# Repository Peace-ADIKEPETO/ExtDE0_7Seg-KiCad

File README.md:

# ExtDE0_7Seg – KiCad port (through-hole, hand-made sandwich PCB)

Extension board for the Terasic **DE0** FPGA board: 4-digit 7-segment display, 8 DIP switches with LEDs, 4 push buttons with LEDs, and a 5-way joystick, all connected through the DE0 40-pin GPIO header.

This repository is a **KiCad re-capture and rework** of the original EPFL/LAP design, adapted to parts that are easy to source in Benin and to a home-made fabrication process.

> **Credit.** The original design is *ExtDE0_7Seg*, EPFL/LAP, R. Beuchat, Rev A, 01/2013 (Altium). The schematic structure and the I/O concept come from that work. Check the original author's licence/terms before publishing this repository, and keep this credit.

## Status

| Item | State |
|---|---|
| Schematic (KiCad, hierarchical, 5 sheets + root) | Done, ERC clean |
| Footprints assigned | Done |
| PCB routing (Freerouting) | Done, GND handled by a pour on B.Cu |
| DRC | 0 errors, 0 unconnected pads, silkscreen warnings only (checked 2026-08-27) |
| Gerber / drill export | Not done yet |
| Board fabricated | No |
| Hardware tested | **No** |

Nothing here has been built or powered yet. See [Known risks](#known-risks-to-check-before-powering-up).

## What changed compared to the original

| Area | Original (2013) | This version | Why |
|---|---|---|---|
| Parts | SMD (0603, SOT-23, resistor arrays) | All through-hole, discrete resistors | Hand soldering, home etching, local sourcing |
| Display | 6-digit KEM-3061-ASR (+ 4-digit LTC4627JR fallback), common anode | One 4-digit 5641AS-style module, **common cathode** | The 6-digit part is not obtainable |
| Digit select | pMOS, active low | nMOS (2N7000), active high | Common cathode must be sunk to GND |
| Segment select | nMOS, active high | pMOS (IRF9520), active low | Common cathode needs segments sourced from 3V3 |
| Reset (discharge) transistors | nMOS | pMOS to 3V3 | Opposite polarity, same purpose |
| P1 header | Generic 2x20 | 2x20 **female** socket (PinSocket 2.54 mm) | Plugs onto the DE0 GPIO pins |
| Fabrication | Industrial 2-layer | Two single-sided boards glued back to back | Material constraint, see below |

### Net names in the KiCad project

The KiCad nets still use some of the original names (`nSelDig0..3`, `SelSeg0..7`, `Reset_Led`) even though the polarity of those lines changed with the common-cathode rework. The names are misleading. Read the table below, not the names.

| Net | Drives | Active level (as built) |
|---|---|---|
| `nSelDig0..3` | Gate of 2N7000 (digit select, source to GND) | **High** |
| `SelSeg0..7` | Gate of IRF9520 (segment, source to 3V3) | **Low** |
| `Reset_Led` | Gates of the 4 reset pMOS (source to 3V3) | **Low** |

Your FPGA code (HDL) must follow these levels. Consider renaming the nets in a later revision.

## Hardware

### Bill of materials (summary)

| Ref | Part | Qty | Package |
|---|---|---|---|
| U1 | 4-digit 7-segment, common cathode (5641AS-style, 0.56") | 1 | THT, custom footprint |
| Digit select | 2N7000 (nMOS) | 4 | TO-92 |
| Segment select | IRF9520 (pMOS) | 8 | TO-220 |
| Reset | IRF9520 (pMOS) | 4 | TO-220 |
| Joystick | Alps SKQUDBE010, 5-way | 1 | Footprint converted from the SMD model, see notes |
| Push buttons | 6x6 mm, 4-pin tactile | 4 | THT |
| DIP switch | 8 positions | 1 | THT |
| LEDs | Yellow, green, orange, red x9 (D1 to D12) | 12 | 3 mm or 5 mm |
| Resistors | 4.7k, 1k, 560R, 330R, 100R, 56R, 0R (axial 1/4 W) | see KiCad BOM | THT |
| P1 | 2x20 female header, 2.54 mm | 1 | THT |

The authoritative list is the BOM exported from KiCad, not this table.

### Sheets

1. **Joystick** – five switches to GND, 4.7k pull-ups to 3V3, outputs `nJoystickN/S/E/W/C` (active low).
2. **Sw_LEDs** – 8-position DIP switch, two resistors and one LED per channel, outputs `Sw_Led0..7`.
3. **LED_Buttons** – 4 buttons with 4.7k pull-ups (`nButton0..3`, active low) and 4 independent LEDs driven by `LedButton0..3`.
4. **6Dig7Seg (4-digit)** – multiplexed display driver: digit-select nMOS, reset pMOS, segment-select pMOS, segment resistors.
5. **Connectors** – P1 (2x20 female) breakout of all nets.

Display multiplexing rule carried over from the original: select one digit at a time, and **never assert the reset transistor together with the digit select** of the same digit. A reset pulse is needed between two digit accesses.

## Fabrication: two-board sandwich

The design is drawn as a normal 2-layer board in KiCad. It is then built as two single-sided boards:

- **F.Cu = Board B**: signal traces, all components.
- **B.Cu = Board A**: GND pour (GND is not routed as traces).
- Every via is a hand-made wire link between the two boards.

Process:

1. Plot F.Cu + Edge.Cuts and B.Cu + Edge.Cuts as two separate artworks.
2. Etch both boards.
3. Clamp the two boards aligned and drill them together from the single drill file.
4. Solder a wire link in each via hole, then insert a thin insulating layer (leaving holes clear) and glue the boards.
5. Solder components from the board B side. Component leads only need to reach board A where the net is GND, or at a via.
6. Check continuity and shorts with a multimeter before applying power.

Design rules used: via 2.0 mm pad / 1.2 mm drill. Component hole minimum was lowered to match real leads. The GND zone uses thermal reliefs on THT pads to make hand soldering easier.

## Repository layout

```
7Seg_Ext.kicad_pro        KiCad project
7Seg_Ext.kicad_sch        root schematic
*.kicad_sch               sub-sheets
7Seg_Ext.kicad_pcb        board layout
docs/                     original PDF schematic (reference)
Gerber files/                   F.Cu and B.Cu plots, drill file (to be generated)
```

## Known risks to check before powering up

- **IRF9520 is not a logic-level MOSFET.** Driven from a 3.3 V FPGA pin its Vgs is only about -3.3 V, close to its threshold range. Segments may be dim or unreliable. Check the datasheet curves, and test one channel on a breadboard first. A logic-level pMOS (or a level-shifting stage) may be needed.
- **The common-cathode rework was derived by reasoning, not copied from the original netlist, and has not been simulated or tested.** Verify the display pinout and the segment/digit mapping against the real module with a multimeter.
- **P1 pin mapping** must match the DE0 GPIO header exactly. Verify every pin against the original PDF Connectors sheet and the DE0 manual before ordering copper.
- **Joystick footprint** was converted from an SMD model. Check pad positions and drill sizes against the Alps datasheet.
- **P1 orientation**: confirm pin 1 position, and that board thickness (two boards + insulator) still lets the socket seat on the DE0.
- **Alignment of the two boards** is the main mechanical risk. Drill them together.

## PCB layout

## PCB 3D Rendering

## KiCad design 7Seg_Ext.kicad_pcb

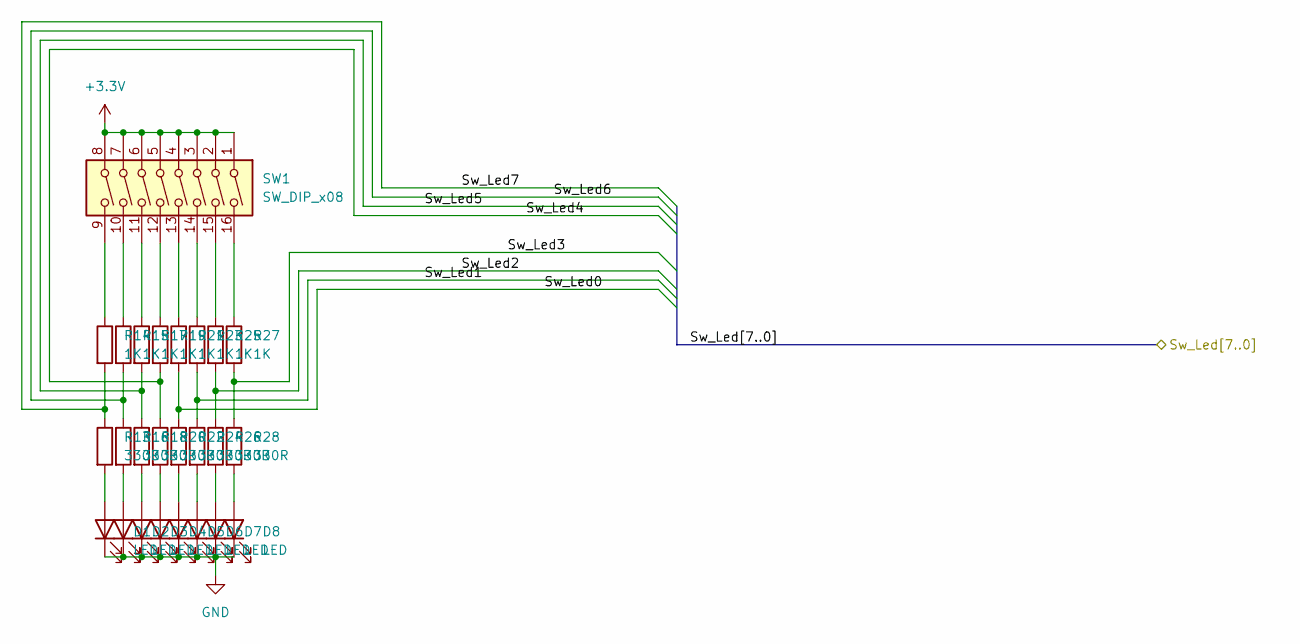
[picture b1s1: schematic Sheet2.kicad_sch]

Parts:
D1, D2, D3, D4, D5, D6, D7, D8: LED; LED_D3.0mm
R13, R16, R18, R20, R22, R24, R26, R28: 330R; R_Axial_DIN0207_L6.3mm_D2.5mm_P10.16mm_Horizontal
R14, R15, R17, R19, R21, R23, R25, R27: 1K; R_Axial_DIN0207_L6.3mm_D2.5mm_P7.62mm_Horizontal
SW1: SW_DIP_x08; SW_DIP_SPSTx08_Slide_9.78x22.5mm_W7.62mm_P2.54mm

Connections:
+3.3V: SW1.1, SW1.2, SW1.3, SW1.4, SW1.5, SW1.6, SW1.7, SW1.8; also elsewhere on the board
/Sw_Led0: R21.2, R22.1; also elsewhere on the board
/Sw_Led1: R23.2, R24.1; also elsewhere on the board
/Sw_Led2: R25.2, R26.1; also elsewhere on the board
/Sw_Led3: R27.2, R28.1; also elsewhere on the board
/Sw_Led4: R19.2, R20.1; also elsewhere on the board
/Sw_Led5: R17.2, R18.1; also elsewhere on the board
/Sw_Led6: R15.2, R16.1
/Sw_Led7: R13.1, R14.2; also elsewhere on the board
GND: D1.1 (K), D2.1 (K), D3.1 (K), D4.1 (K), D5.1 (K), D6.1 (K), D7.1 (K), D8.1 (K); also elsewhere on the board
unnamed: D1.2 (A), R13.2
unnamed: D2.2 (A), R16.2
unnamed: D3.2 (A), R18.2
unnamed: D4.2 (A), R20.2
unnamed: D5.2 (A), R22.2
unnamed: D6.2 (A), R24.2
unnamed: D7.2 (A), R26.2
unnamed: D8.2 (A), R28.2
unnamed: R14.1, SW1.9
unnamed: R15.1, SW1.10
unnamed: R17.1, SW1.11
unnamed: R19.1, SW1.12
unnamed: R21.1, SW1.13
unnamed: R23.1, SW1.14
unnamed: R25.1, SW1.15
unnamed: R27.1, SW1.16

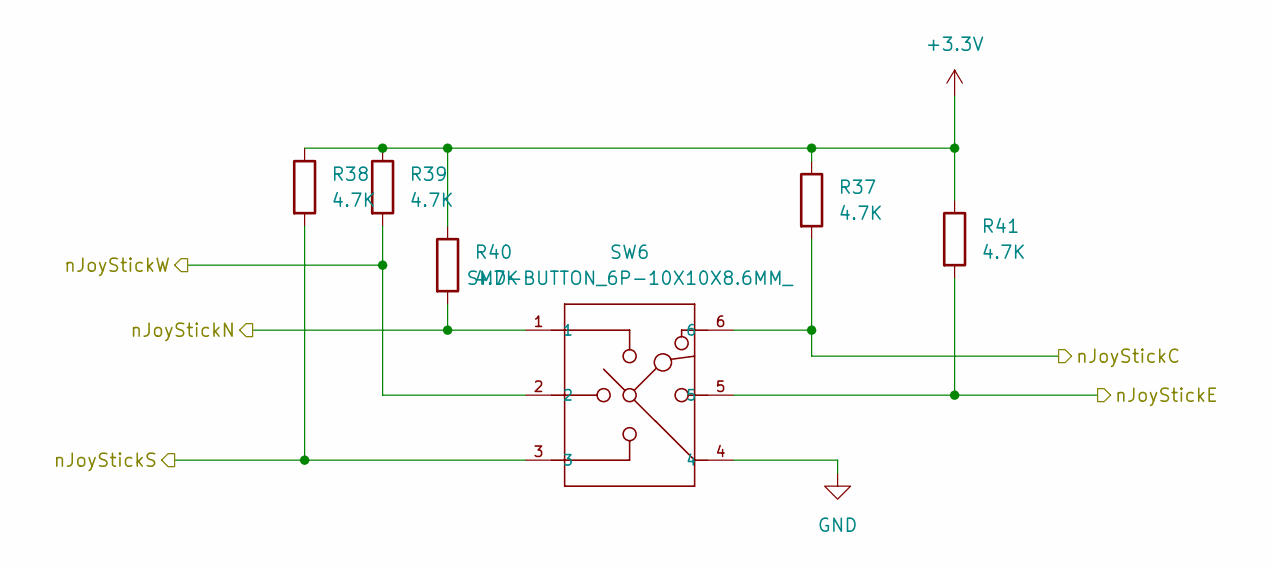
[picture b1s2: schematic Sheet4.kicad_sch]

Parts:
R37, R38, R39, R40, R41: 4.7K; R_Axial_DIN0207_L6.3mm_D2.5mm_P7.62mm_Horizontal
SW6: SMD-BUTTON_6P-10X10X8.6MM_; SW6-3.25-10X10X8.6MM

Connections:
+3.3V: R37.1, R38.1, R39.1, R40.1, R41.1; also elsewhere on the board
/nJoyStickC: R37.2, SW6.6; also elsewhere on the board
/nJoyStickE: R41.2, SW6.5; also elsewhere on the board
/nJoyStickN: R40.2, SW6.1; also elsewhere on the board
/nJoyStickS: R38.2, SW6.3; also elsewhere on the board
/nJoyStickW: R39.2, SW6.2; also elsewhere on the board
GND: SW6.4; also elsewhere on the board

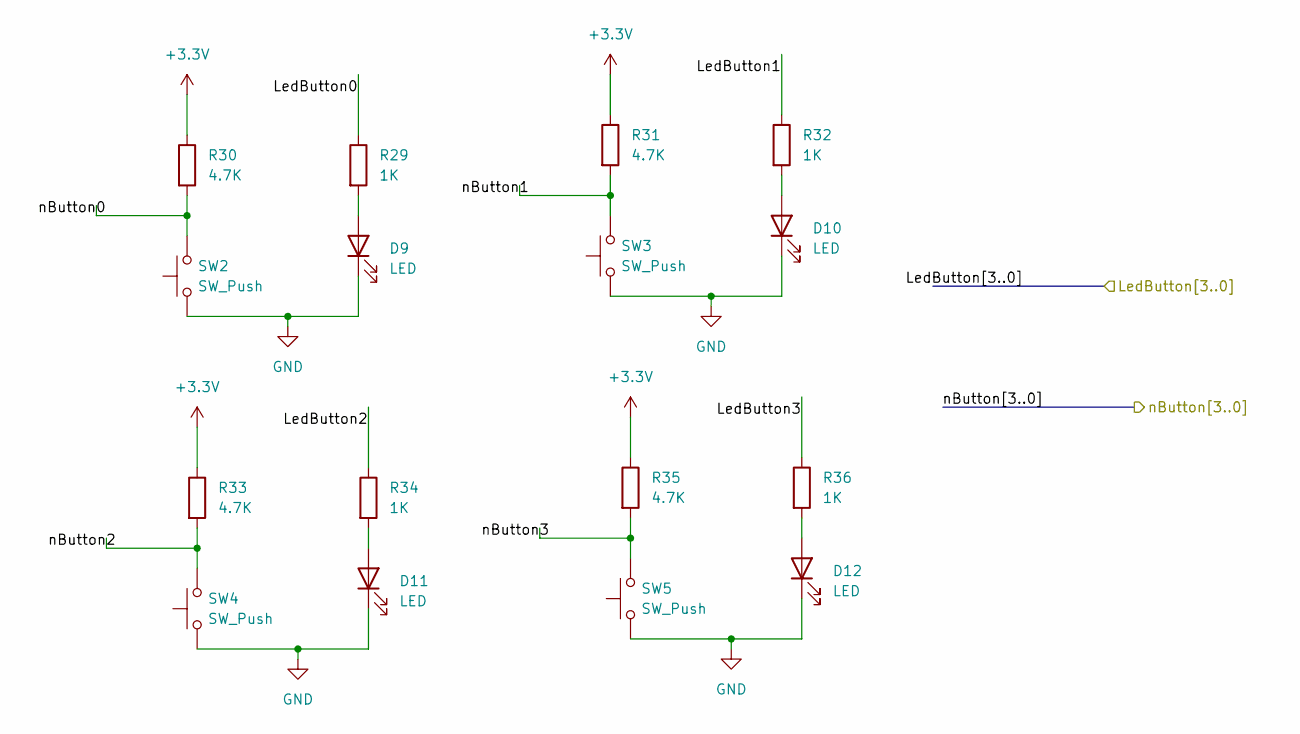
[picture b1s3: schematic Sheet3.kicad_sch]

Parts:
D9, D10, D11, D12: LED; LED_D3.0mm
R29, R32, R34, R36: 1K; R_Axial_DIN0207_L6.3mm_D2.5mm_P7.62mm_Horizontal
R30, R31, R33, R35: 4.7K; R_Axial_DIN0207_L6.3mm_D2.5mm_P7.62mm_Horizontal
SW2, SW3, SW4, SW5: SW_Push; SW_PUSH_6mm

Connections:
+3.3V: R30.1, R31.1, R33.1, R35.1; also elsewhere on the board
/LedButton0: R29.1; also elsewhere on the board
/LedButton1: R32.1; also elsewhere on the board
/LedButton2: R34.1; also elsewhere on the board
/LedButton3: R36.1; also elsewhere on the board
/nButton0: R30.2, SW2.2; also elsewhere on the board
/nButton1: R31.2, SW3.2; also elsewhere on the board
/nButton2: R33.2, SW4.2; also elsewhere on the board
/nButton3: R35.2, SW5.2; also elsewhere on the board
GND: D9.1 (K), D10.1 (K), D11.1 (K), D12.1 (K), SW2.1, SW3.1, SW4.1, SW5.1; also elsewhere on the board
unnamed: D9.2 (A), R29.2
unnamed: D10.2 (A), R32.2
unnamed: D11.2 (A), R34.2
unnamed: D12.2 (A), R36.2

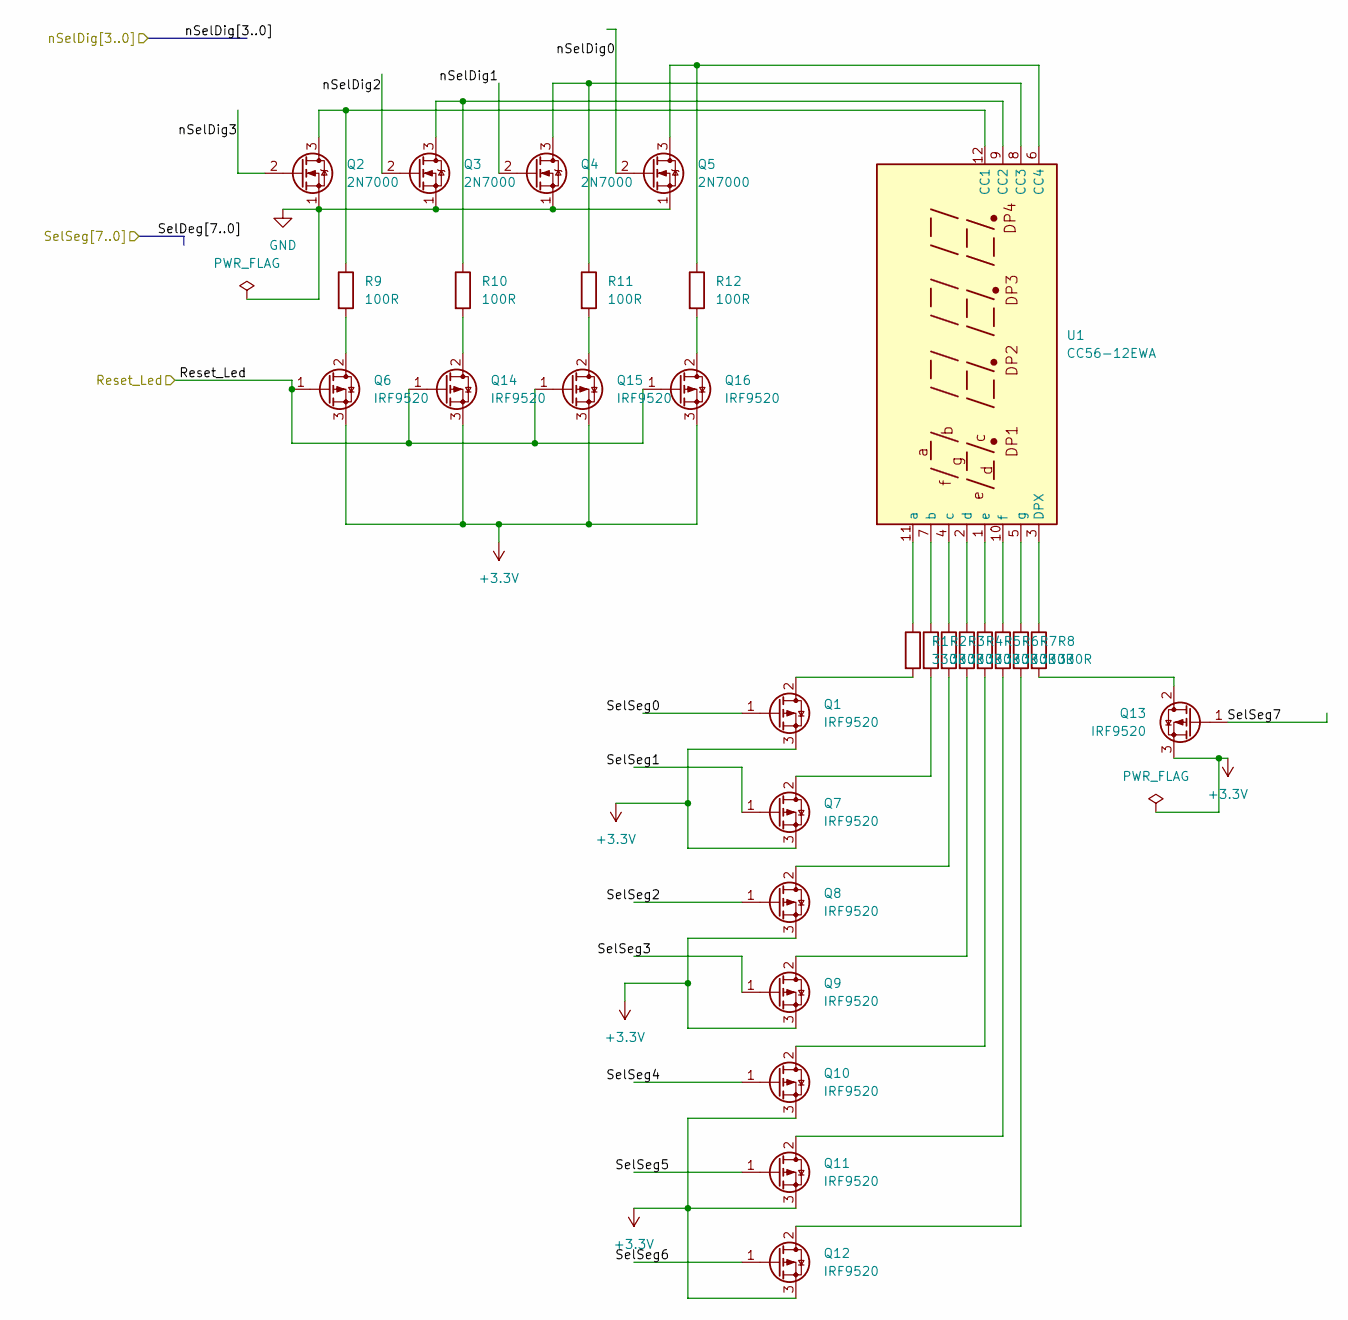
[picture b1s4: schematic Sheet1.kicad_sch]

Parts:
Q1, Q6, Q7, Q8, Q9, Q10, Q11, Q12, Q13, Q14, Q15, Q16: IRF9520; TO-220-3_Vertical
Q2, Q3, Q4, Q5: 2N7000; TO-92_Inline
R1, R2, R3, R4, R5, R6, R7, R8: 330R; R_Axial_DIN0207_L6.3mm_D2.5mm_P10.16mm_Horizontal
R9, R10, R11, R12: 100R; R_Axial_DIN0207_L6.3mm_D2.5mm_P7.62mm_Horizontal
U1: CC56-12EWA; CA56-12EWA

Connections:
+3.3V: Q1.3 (S), Q6.3 (S), Q7.3 (S), Q8.3 (S), Q9.3 (S), Q10.3 (S), Q11.3 (S), Q12.3 (S), Q13.3 (S), Q14.3 (S), Q15.3 (S), Q16.3 (S); also elsewhere on the board
/Reset_Led: Q6.1 (G), Q14.1 (G), Q15.1 (G), Q16.1 (G); also elsewhere on the board
/SelSeg0: Q1.1 (G); also elsewhere on the board
/SelSeg1: Q7.1 (G); also elsewhere on the board
/SelSeg2: Q8.1 (G); also elsewhere on the board
/SelSeg3: Q9.1 (G); also elsewhere on the board
/SelSeg4: Q10.1 (G); also elsewhere on the board
/SelSeg5: Q11.1 (G); also elsewhere on the board
/SelSeg6: Q12.1 (G); also elsewhere on the board
/SelSeg7: Q13.1 (G); also elsewhere on the board
/nSelDig0: Q5.2 (G); also elsewhere on the board
/nSelDig1: Q4.2 (G); also elsewhere on the board
/nSelDig2: Q3.2 (G); also elsewhere on the board
/nSelDig3: Q2.2 (G); also elsewhere on the board
GND: Q2.1 (S), Q3.1 (S), Q4.1 (S), Q5.1 (S); also elsewhere on the board
unnamed: Q1.2 (D), R1.2
unnamed: Q2.3 (D), R9.1, U1.12 (CC1)
unnamed: Q3.3 (D), R10.1, U1.9 (CC2)
unnamed: Q4.3 (D), R11.1, U1.8 (CC3)
unnamed: Q5.3 (D), R12.1, U1.6 (CC4)
unnamed: Q6.2 (D), R9.2
unnamed: Q7.2 (D), R2.2
unnamed: Q8.2 (D), R3.2
unnamed: Q9.2 (D), R4.2
unnamed: Q10.2 (D), R5.2
unnamed: Q11.2 (D), R6.2
unnamed: Q12.2 (D), R7.2
unnamed: Q13.2 (D), R8.2
unnamed: Q14.2 (D), R10.2
unnamed: Q15.2 (D), R11.2
unnamed: Q16.2 (D), R12.2
unnamed: R8.1, U1.3 (DPX)
unnamed: R1.1, U1.11 (a)
unnamed: R2.1, U1.7 (b)
unnamed: R3.1, U1.4 (c)
unnamed: R4.1, U1.2 (d)
unnamed: R5.1, U1.1 (e)
unnamed: R6.1, U1.10 (f)
unnamed: R7.1, U1.5 (g)

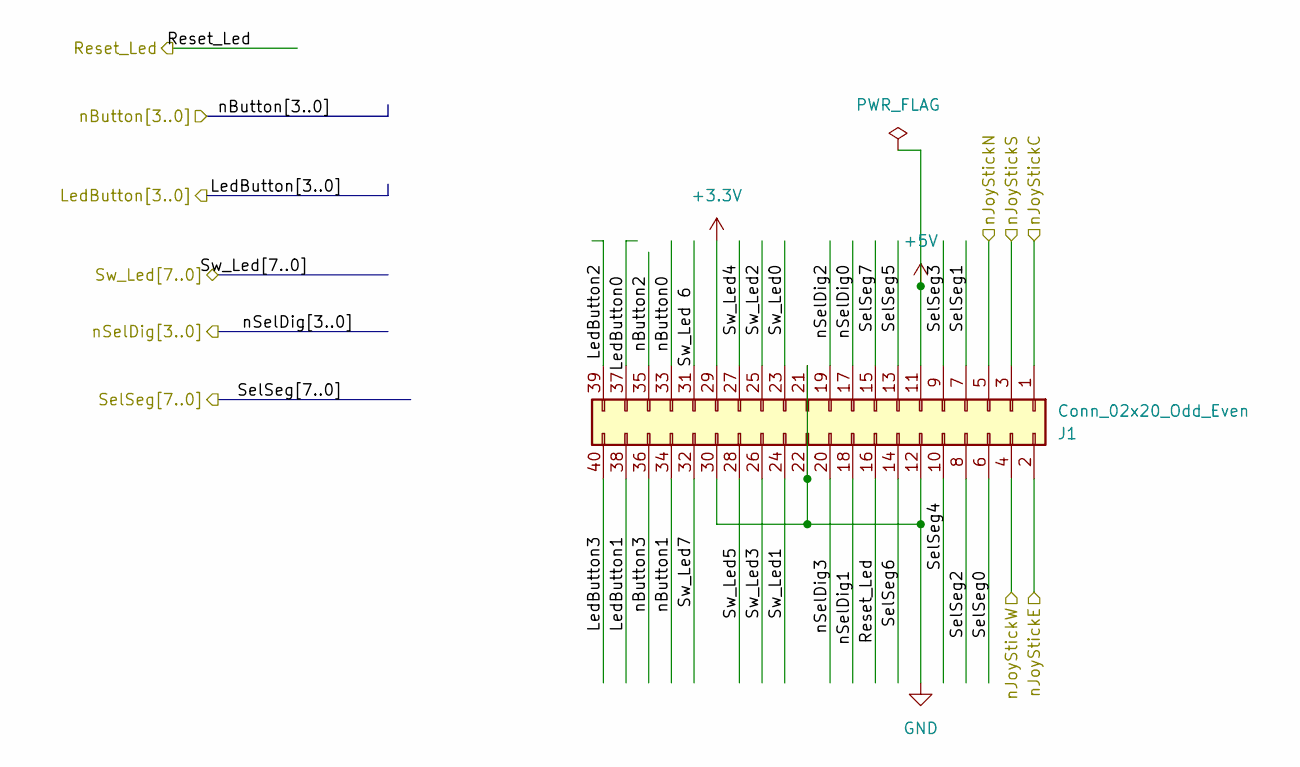
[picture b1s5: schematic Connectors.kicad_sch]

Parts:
J1: Conn_02x20_Odd_Even; PinSocket_2x20_P2.54mm_Vertical

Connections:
+3.3V: J1.29; also elsewhere on the board
+5V: J1.11
/Connectors/Sw_Led 6: J1.31
/LedButton0: J1.37; also elsewhere on the board
/LedButton1: J1.38; also elsewhere on the board
/LedButton2: J1.39; also elsewhere on the board
/LedButton3: J1.40; also elsewhere on the board
/Reset_Led: J1.16; also elsewhere on the board
/SelSeg0: J1.6; also elsewhere on the board
/SelSeg1: J1.7; also elsewhere on the board
/SelSeg2: J1.8; also elsewhere on the board
/SelSeg3: J1.9; also elsewhere on the board
/SelSeg4: J1.10; also elsewhere on the board
/SelSeg5: J1.13; also elsewhere on the board
/SelSeg6: J1.14; also elsewhere on the board
/SelSeg7: J1.15; also elsewhere on the board
/Sw_Led0: J1.23; also elsewhere on the board
/Sw_Led1: J1.24; also elsewhere on the board
/Sw_Led2: J1.25; also elsewhere on the board
/Sw_Led3: J1.26; also elsewhere on the board
/Sw_Led4: J1.27; also elsewhere on the board
/Sw_Led5: J1.28; also elsewhere on the board
/Sw_Led7: J1.32; also elsewhere on the board
/nButton0: J1.33; also elsewhere on the board
/nButton1: J1.34; also elsewhere on the board
/nButton2: J1.35; also elsewhere on the board
/nButton3: J1.36; also elsewhere on the board
/nJoyStickC: J1.1; also elsewhere on the board
/nJoyStickE: J1.2; also elsewhere on the board
/nJoyStickN: J1.5; also elsewhere on the board
/nJoyStickS: J1.3; also elsewhere on the board
/nJoyStickW: J1.4; also elsewhere on the board
/nSelDig0: J1.17; also elsewhere on the board
/nSelDig1: J1.18; also elsewhere on the board
/nSelDig2: J1.19; also elsewhere on the board
/nSelDig3: J1.20; also elsewhere on the board
GND: J1.12, J1.21, J1.22, J1.30; also elsewhere on the board

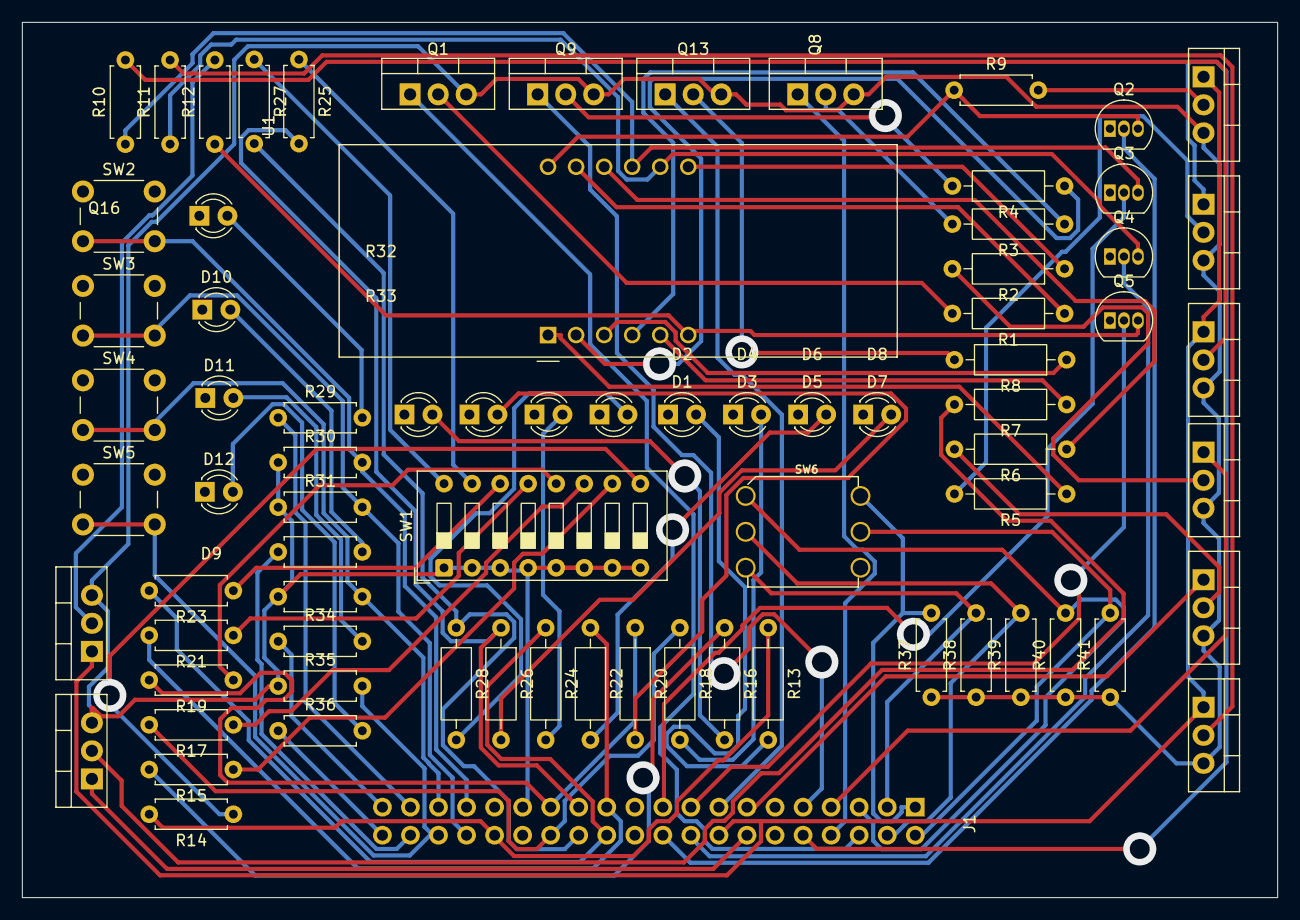
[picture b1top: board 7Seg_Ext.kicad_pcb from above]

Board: 2 copper layers, 113.7 x 79.3 mm, 77 parts (1 on the bottom side), 80 nets.
